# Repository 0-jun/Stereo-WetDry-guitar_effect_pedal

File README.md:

Stereo Wet/Dry pedal
=======================
The effect pedal has the following functions.
* Dry_In : Split dry signal to sum into each channel of the stereo wet signal
* Dry_Buffered_Bypass (DBD) : Output buffered dry signal for using input of another pedal
* Wet_Right_In (WR In), Wet_Left_In (WL In) : Stereo input for signals such as delay, reverb, chorus, etc
* WRD_Out, WLD_Out : Output stereo of wet+dry signal (or you can use it as a mono using only one channel)
* Four volume knob : Set the volume of two dry signals and two wet signals by knob

## PCB
I divided the pcb into three to put all parts in the pedal case.
1. power part

2. register for half vdd inputa

3. main part (opamp)

## Verify signal
1.Verify Dry_In (triangle wave) signal and Dry_Buffered_Bypass
 * blue signal : Dry_In (STM32 DAC out (triangle wave))
 * yellow signal : Dry_Buffered_Bypass

2. Verify Dry_In signal (triangle wave) and WRD_Out signal (guitar signal) mixed
 * blue signal : Dry_In (STM32 DAC out (triangle wave))
 * yellow signal : WRD_Out (blue signal + guitar signal)

## Conclusion
It was confirmed that the dry signal and the wet signal were mixed when connected in the following configuration.\
Also, it can be used channel2 of U2(OPAMP) for Dry_Buffered_Byass2.

### configuration
* config1

* config2

* config3

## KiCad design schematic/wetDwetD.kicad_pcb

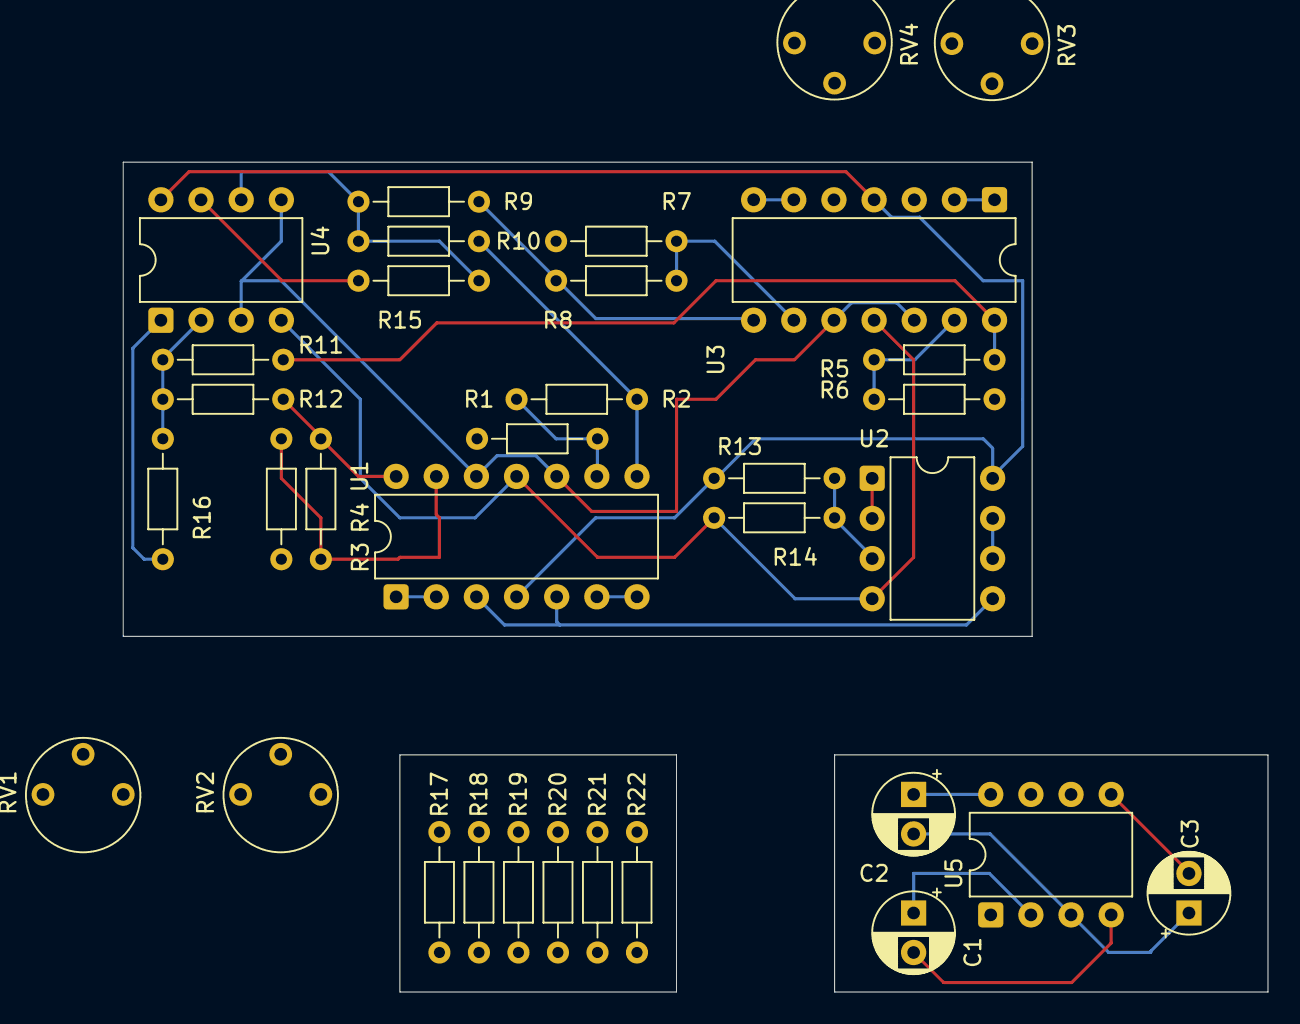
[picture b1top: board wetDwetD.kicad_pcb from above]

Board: 2 copper layers, 72.4 x 52.5 mm, 34 parts (0 on the bottom side), 31 nets.

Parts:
C1, C2, C3: C_Polarized_US; CP_Radial_D5.0mm_P2.50mm
R1, R2, R3, R4, R5, R6, R7, R8, R9, R10, R11, R12, R15, R16: 10k ohm; R_Axial_DIN0204_L3.6mm_D1.6mm_P7.62mm_Horizontal
R13, R14: R_US; R_Axial_DIN0204_L3.6mm_D1.6mm_P7.62mm_Horizontal
R17, R18, R19, R20, R21, R22: 1M ohm; R_Axial_DIN0204_L3.6mm_D1.6mm_P7.62mm_Horizontal
RV1, RV2, RV3, RV4: R_Potentiometer_US; Potentiometer_Vishay_T7-YA_Single_Vertical
U1, U3: TL074; DIP-14_W7.62mm
U2, U4: TL072; DIP-8_W7.62mm
U5: LT1054; DIP-8_W7.62mm

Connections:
+9V: C2.1, R13.1, R17.1, R19.1, R21.1, U1.4 (V+), U2.8 (V+), U3.4 (V+), U4.8 (V+), U5.8 (V+)
-9V: C3.2, R14.2, R18.2, R20.2, R22.2, U1.11 (V-), U2.4 (V-), U3.11 (V-), U4.4 (V-), U5.5 (-VOUT)
/DryL: R2.1, R10.2, U1.8
/DryR: R4.1, R12.2, U1.14
/Dry_Buffered_Bypass: U2.6 (-), U2.7
/Dry_In: R17.2, R18.1, U1.3 (+), U1.5 (+), U2.5 (+)
/WDL_Out: R16.1, U4.1
/WDR_Out: R15.1, U4.7
/WetL_Inv: R8.1, R9.2, U3.8
/WetR_Inv: R6.1, R11.2, U3.14
/Wet_Left_In: R21.2, R22.1, U3.5 (+)
/Wet_Right_In: R19.2, R20.1, U3.3 (+)
GND: C2.2, C3.1, RV1.3, RV2.3, RV3.3, RV4.3, U1.10 (+), U1.12 (+), U3.10 (+), U3.12 (+), U4.3 (+), U4.5 (+), U5.3 (GND)
unnamed: R1.2, RV2.2
unnamed: R3.2, RV1.2
unnamed: R5.2, RV3.2
unnamed: R7.2, RV4.2
unnamed: RV1.1, U1.1, U1.2 (-)
unnamed: RV2.1, U1.6 (-), U1.7
unnamed: R1.1, R2.2, U1.9 (-)
unnamed: R3.1, R4.2, U1.13 (-)
unnamed: R13.2, R14.1, U2.3 (+)
unnamed: U2.1, U2.2 (-)
unnamed: RV3.1, U3.1, U3.2 (-)
unnamed: RV4.1, U3.6 (-), U3.7
unnamed: R7.1, R8.2, U3.9 (-)
unnamed: R5.1, R6.2, U3.13 (-)
unnamed: R11.1, R12.1, R16.2, U4.2 (-)
unnamed: R9.1, R10.1, R15.2, U4.6 (-)
unnamed: C1.1, U5.2 (CAP+)
unnamed: C1.2, U5.4 (CAP-)

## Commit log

2025-04-05 Add image (signal)
2025-04-05 Change image name
2025-04-06 Modify git ignore for local directory
2025-04-06 Add pedal chain image
2025-04-06 Add PCB image
2025-04-06 Change image
2025-04-06 Update README (add image with description)
2025-04-06 Modify main part pcb (rotate)
2025-04-06 Fix image (change direction of port)
2025-04-06 Rename config1.png to config 1.png
2025-04-06 Rename config2.png to config 2.png
2025-04-06 Rename config3.png to config 3.png
2025-04-06 Rename PCB-main part.jpg to PCB-main part .jpg
